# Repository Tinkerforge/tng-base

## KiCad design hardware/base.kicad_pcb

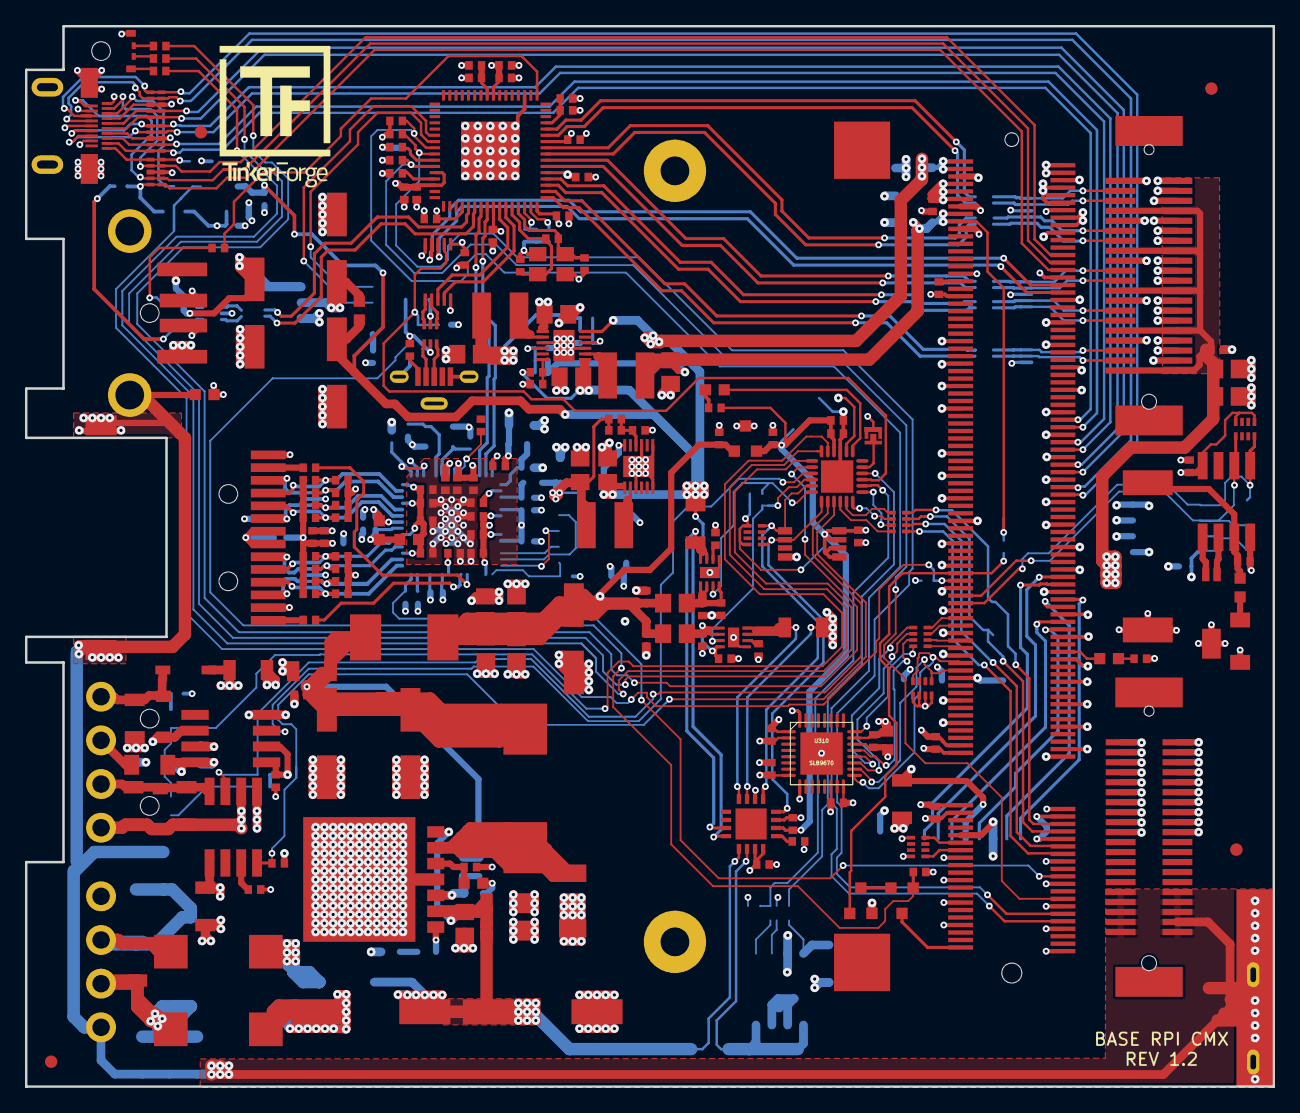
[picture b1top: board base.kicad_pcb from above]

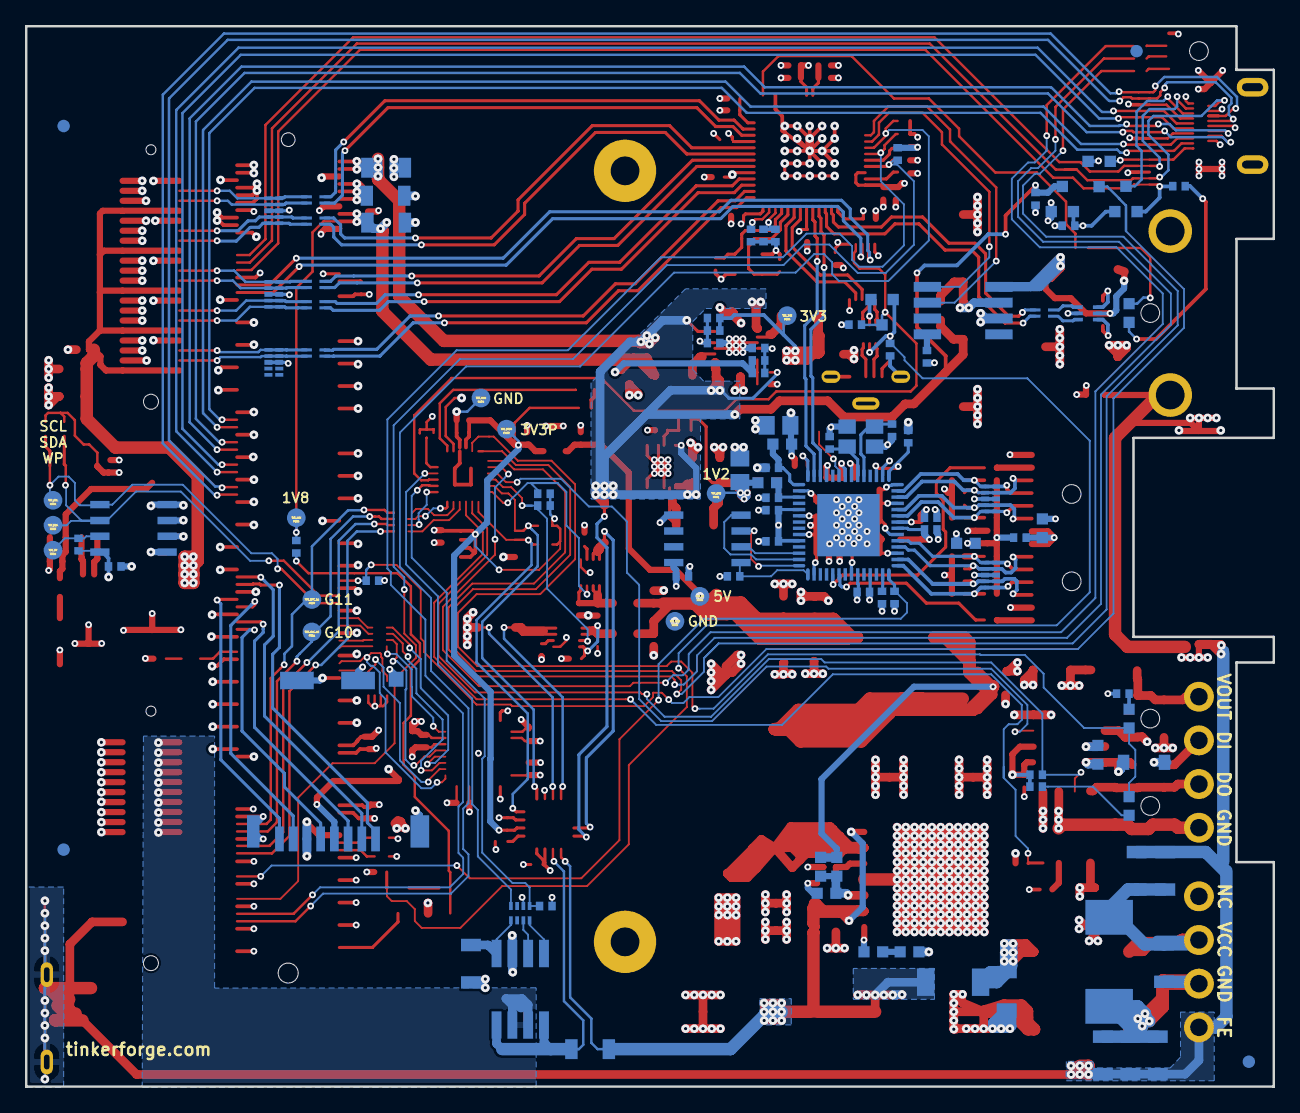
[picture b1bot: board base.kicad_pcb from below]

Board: 4 copper layers, 100.0 x 85.0 mm, 315 parts (112 on the bottom side), 207 nets.

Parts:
C101, C102, C421, C422: 33pF; C0402F
C103, C105, C115, C119, C122, C123, C124, C125, C126, C127, C128, C129, C130, C134, C307, C308, C310: 1uF; C0402F
C104, C106, C107, C110, C111, C112, C113, C114, C116, C118, C121, C133, C214, C221, C222, C227, C302, C315, C316, C318, C319, C321, C323, C325, C327, C402, C403, C404, C405, C406, C407, C408, C409, C411, C412, C413, C414, C415, C416, C417, C418, C419, C420, C430, C433: 100nF; C0402F
C108, C109, C117, C216, C219, C220: 100uF; ELKO_63
C120: 100nF; C0603F
C131, C132, C322, C324: DNP; C0402F
C135, C136, C218, C223, C224, C225, C301, C303, C309, C311, C401, C410, C435, C437: 10uF; C0805E
C201, C202, C203: 10uF/35V; C1206
C204, C211: 10nF; C1206
C205: 100nF/35V; C0805E
C206, C207: 1nF 2kV; C1206
C208, C305, C306, C436: 100pF; C0402F
C209: 1uF/50V; C1206
C210: 4.7nF; C0603F
C212, C213: UWT1H221MNL1GS; ELKO_103
C215, C226: 10uF; C1206
C217: DNP; C0603F
C304, C312, C313, C314: 47uF; C1206
C317: DSK-3R3H334T-HL; DSK
C320: 2.2uF; C0603F
C423, C424, C425, C426, C427, C429, C431, C432: 15pF/50V; C0402F
C428: 10nF; C0402F
C434: 22nF/50V; C0603F
D101: LED green; LED-LP
D201: 3.0SMI30CATR; SMC
D202, D204, D209: SMF36CA; SOD-123FL
D203: SBR0560S1-7; SOD-123
D205, D206: PMEG6045; SOD-128
D207, D210: LED; LED-LP
D208: LED; D0603F
D301: green; D0603F
D302: BAQ33-GS08; MiniMelf
Fiducial_Mark: VAL**; Fiducial_Mark
Fiducial_Mark#2, Fiducial_Mark#3, Fiducial_Mark#4, Fiducial_Mark#5, Fiducial_Mark#6, Fiducial_Mark#7, Fiducial_Mark#8: VAL**; Fiducial_Mark
J101: USB-A; USB-A-SMT-8231
J102: TNG-Data-TOP; TNG-40-TOP
J103: TNG-Power-TOP; TNG-40-TOP
J301: MICROSDCARD; SD-Card-DM3CS
J302: Raspberry-Pi-Compute-Socket
J303: MICRO_HDMI; MICRO-HDMI-D
J304: USB Micro; USB-Micro-Vertical
J401: RJSLG-001TA1
L101: INDUCTs; R0603F
L102, L103, L104, L105, L106, L107: 744230900; WE-CNSW-0603
L108, L109: 742792040; R0805E
L202: 22uH 74437368220; WE-LHMI
L203: 10uH; SRP7030
L301: 4.7uH; NR4040
L302, L406: 2.2uH; NR4040
L401, L402, L403, L404, L405: FB; R0603F
LED101: EASV3015RGBA0; LED-RGB-LP
P101: Debug; DEBUG_PAD
P102: Boot; SolderJumper
P103: PE; PE_Hook
P104, P204: TST_GND; TSTPT
P105: TST_3V3P; TSTPT
P201: DI IN; OQ_4P
P202: PWR IN; OQ_4P
P203: TST_5V; TSTPT
P301: TST_XMC_10; TSTPT
P302: TST_SCL; TSTPT
P303: TST_SDA; TSTPT
P304: TST_WP; TSTPT
P305: TST_3V3; TSTPT
P306: TST_1V8; TSTPT
P307: TST_XMC_11; TSTPT
P401: TST_1V2; TSTPT
Q301, Q302, Q303, Q304, Q305: 2N7002P; SOT23GDS
R101, R105, R106, R107, R108, R111, R115, R116, R117, R218, R305, R320, R401, R402, R406, R414: 10k; R0402F
R102, R210, R301, R302, R304, R316, R419, R420: 100k; R0402F
R103: 1M; R0402F
R104, R213, R216, R217, R222, R309, R416, R417: 1k; R0402F
R109, R403: DNP; R0402F
R110, R405: 12k; R0402F
R112, R113, R315: 0; R0402F
R114: 56; R0402F
R118: 1k; R1206
R201, R202, R204, R206, R207: VC1206K201R030; R1206
R203: 1k; RMELF
R205: 562; R0603F
R208: 27k; R0603F
R209: 1M; R1206
R211: 562; R0402F
R212: 20k; R0603F
R214: 47k; R0603F
R215: 8.2k; R0603F
R219, R220, R221: 0.02; R1206
R303: 120k; R0402F
R306: 536k; R0402F
R307: 200k; R0402F
R313, R317, R318: 47k; R0402F
R314: 68; R0603F
R319: 27k; R0402F
R404: 8.06k; R0402F
R407, R408, R409, R410, R411, R412, R413, R415: 49.9; R0402F
R418: 10; R0402F
RP101, RP102, RP303, RP305: 10k; 4X0402
RP301, RP304: 82; 4X0402
RP302: 100k; 4X0402
T201: 744272251; WE-SL5
U101: USB2517; QFN64-9x9mm-0.5mm_USB2517
U102: MIC2026-1YM; SO-8
U103, U307: 82400152; SOT563-SPEC
U104: XMC1302; QFN24-4x4mm-0.5mm
U105, U106, U107, U304, U305, U306, U403, U404: TPD4S010DQA
U108: AP7333-33SAG-7; SOT23-3
U109, U110: TPS22975; WSON8-2x2
U111: PCT2075DP; TSSOP8_3
U112: VN7140AS; SO-8
U201: ISO1211; SO-8
U202: FPF2700MX; SO-8
U203: BD90640HFP; BD906XX-C-HRP7
U204: PAC1933; QFN-16
U301, U405: PAM2306AYPAA; WDFN12-3x3-0.45
U302: PCF8523T; SO-8
U303: FSUSB42MUX; MSOP10-0.5
U308: M24256-DFMN6TP; SOIC8
U309: AP2331; SOT23-3
U310: SLB9670; QFN32-EXT
U401: LAN7500; QFN56-8x8mm-0.5mm
U402: 93AA66; SOIC8
X101: 24MHz; CRYSTAL_3225
X301: 32.768kHz; AB26TRQ
X401: 25MHz_18pF; CRYSTAL_3225

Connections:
3V3: C110.1, C111.1, C112.1, C113.1, C114.1, C115.1, C116.1, C118.1, C119.1, C304.1, C305.1, C307.1, C308.2, C309.1, C310.1, C313.1, C315.1, C318.2, C319.2, C320.2, C322.1, C323.1, C324.1, C325.1, C401.1, C402.1, C403.1, C404.1, C406.1, C433.1, D101.1, D302.1, J301.4, J302.39, J302.40, J302.41, J302.42, J302.189, J302.190, J302.191, J302.192, J302.193, J302.194, J401.12, J401.14, L301.2, L403.2, L405.1, P305.1, R101.2, R102.2, R106.2, R108.2, R111.2, R305.1, R306.1, R309.2, R316.1, R317.2, R319.1, R401.2, R402.2, R406.1, RP303.1, RP303.4, RP305.1, RP305.2, RP305.3, RP305.4, U101.5, U101.10, U101.24, U101.44, U101.46, U101.52, U101.57, U101.64, U302.8, U303.1, U308.8, U310.1, U310.8, U310.14, U310.22, U401.7, U401.19, U401.24, U401.37, U402.8
3V3_PERM: C121.1, C122.1, C130.1, C133.1, C221.1, C222.1, C227.2, LED101.1, P105.1, R115.2, R116.2, R117.2, R210.2, R213.1, R216.2, R217.2, RP101.5, RP101.8, RP102.2, U104.10, U108.2, U111.5, U111.6, U111.7, U111.8, U201.1, U201.2, U204.2, U204.6, U204.15, U204.16
5VSW: C108.1, C301.1, C303.1, C314.1, C321.1, C435.1, J302.197, J302.198, J302.199, J302.200, L101.2, R219.2, R301.2, U204.12, U301.1, U301.6, U301.7, U309.3, U405.6, U405.7
5VStack: C134.2, C135.2, C136.2, J102.7, J102.8, J102.15, J102.16, J102.23, J102.24, J102.31, J102.32, J102.39, J102.40, R221.2, U204.7
+1.2V: C410.1, C411.1, C412.1, C413.1, C414.1, C415.1, C417.1, C418.1, C436.1, C437.1, L401.2, L402.2, L404.2, L406.2, P401.1, R420.1, U401.8, U401.11, U401.20, U401.23, U401.30, U401.36, U401.49
+1.2V_INT: C405.1, C407.1, C408.1, C409.1, L401.1, U401.45, U401.48, U401.53, U401.56
+1.8V: C306.1, C311.1, C312.1, J302.183, J302.184, J302.185, J302.186, L302.2, P306.1, R304.2, R307.1
+3.3VP: C420.1, L403.1, U401.15
+5V: C123.2, C125.2, C129.1, C218.1, C219.1, C223.1, C224.1, C225.1, L108.1, L109.1, L203.2, P203.1, U108.1
AGND: C101.2, C102.2, C103.2, C104.2, C105.2, C106.2, C107.2, C108.2, C109.2, C110.2, C111.2, C112.2, C113.2, C114.2, C115.2, C116.2, C117.2, C118.2, C119.2, C120.2, C121.2, C122.2, C123.1, C124.1, C125.1, C126.1, C127.2, C128.2, C129.2, C130.2, C131.2, C132.2, C133.2, C134.1, C135.1, C136.1, C201.2, C202.2, C203.1, C205.2, C208.2, C209.2, C210.2, C211.2, C212.2, C213.2, C214.2, C215.2, C216.2, C218.2, C219.2, C220.2, C221.2, C222.2, C223.2, C224.2, C225.2, C226.1, C227.1, C301.2, C302.2, C303.2, C304.2, C307.2, C308.1, C309.2, C310.2, C311.2, C312.2, C313.2, C314.2, C315.2, C316.2, C317.2, C318.1, C319.1, C320.1, C321.2, C322.2, C323.2, C324.2, C325.2, C327.2, C401.2, C402.2, C403.2, C404.2, C405.2, C406.2, C407.2, C408.2, C409.2, C410.2, C411.2, C412.2, C413.2, C414.2, C415.2, C416.2, C417.2, C418.2, C419.2, C420.2, C421.2, C422.2, C423.2, C424.2, C425.2, C426.2, C427.2, C428.2, C429.2, C430.2, C431.2, C432.2, C433.2, C434.2, C435.2, C437.2, D202.2, D204.2, D206.1, D209.2, J101.4, J102.1, J102.2, J102.4, J102.6, J102.9, J102.10, J102.12, J102.14, J102.17, J102.18, J102.20, J102.22, J102.25, J102.26, J102.28, J102.30, J102.33, J102.34, J102.36, J102.38, J103.2, J103.4, J103.6, J103.8, J103.10, J103.12, J103.14, J103.16, J103.18, J103.20, J301.6, J301.S, J302.1, J302.7, J302.8, J302.13, J302.14, J302.19, J302.20, J302.25, J302.26, J302.31, J302.32, J302.37, J302.38, J302.43, J302.44, J302.49, J302.50, J302.55, J302.56, J302.61, J302.62, J302.67, J302.68, J302.73, J302.74, J302.79, J302.80, J302.85, J302.86, J302.91, J302.92, J302.97, J302.98, J302.103, J302.104, J302.109, J302.110, J302.115, J302.116, J302.121, J302.122, J302.127, J302.133, J302.134, J302.139, J302.140, J302.145, J302.146, J302.151, J302.152, J302.157, J302.163, J302.164, J302.169, J302.170, J302.181, J302.182, J302.187, J302.188, J302.195, J302.196, J303.4, J303.7, J303.10, J303.13, J303.16, J303.SHD, J304.5, J304.6, P102.1, P104.1, P201.4, P204.1, Q301.S, Q303.S, Q304.S, R105.1, R107.2, R109.2, R110.1, R118.1, R201.1, R202.2, R208.1, R211.2, R215.1, R218.2, R222.2, R302.1, R303.1, R313.1, R315.1, R318.1, R404.1, R405.1, R414.1, R419.1, RP302.5, RP302.8, T201.1, U101.19, U101.EXP, U102.6, U103.2, U104.9, U104.EXP, U105.3, U105.8, U106.3, U106.8, U107.3, U107.8, U108.3, U109.5, U109.EXP, U110.5, U110.EXP, U111.4, U112.3, U201.4, U201.6, U202.5, U202.6, U203.4, U203.EXP, U204.3, U301.3, U301.9, U301.EP, U302.4, U303.5, U303.10, U304.3, U304.8, U305.3, U305.8, U306.3, U306.8, U307.2, U308.1, U308.2, U308.3, U308.4, U309.1, U310.2, U310.9, U310.16, U310.23, U310.32, U310.33, U401.2, U401.39, U401.EP, U402.5, U403.3, U403.8, U404.3, U404.8, U405.1, U405.3, U405.9, U405.12, U405.EP, X101.3, X301.3, X401.3
CUR1+: R219.1, U109.7, U109.8, U204.11
CUR2+: C201.1, C202.1, C203.2, C205.1, C212.1, C213.1, C226.2, D203.1, D205.2, R220.1, U202.1, U203.2, U203.7, U204.13
CUR2-: R220.2, U112.5, U112.8, U204.14
CUR3+: R221.1, U110.7, U110.8, U204.8
EECLK: U401.26, U402.2
EECS: R414.2, U401.29, U402.1
EEDI: U401.27, U402.4
EEDO: U401.28, U402.3
ETH_RESET: J302.21, R401.1, U401.42
ETH_USB_D+: U101.56, U401.13
ETH_USB_D-: U101.55, U401.12
EXT_USB_D+: L102.2, U101.54
EXT_USB_D-: L102.3, U101.53
EXT_USB_D_F+: J101.3, U103.4
EXT_USB_D_F-: J101.2, U103.6
Earth: C120.1, C206.2, C207.1, J101.SHD, J103.31, J103.32, J103.33, J103.34, J103.35, J103.36, J103.37, J103.38, J103.39, J103.40, J401.SHD, P103.1, P202.4, R206.2, R207.1, R209.1
FLASH_USB_D+: U303.7, U307.1
FLASH_USB_D-: U303.6, U307.3
FLASH_USB_D_F+: J304.3, U307.6
FLASH_USB_D_F-: J304.2, U307.4
HDMI_5V: C327.1, J303.19, Q305.G, U309.2
HDMI_CEC: J302.171, Q305.S, R319.2, U306.1, U306.10
HDMI_CLK+: J302.113, J303.12, U305.4, U305.7
HDMI_CLK-: J302.111, J303.14, U305.5, U305.6
HDMI_D0+: J302.119, J303.9, U305.1, U305.10
HDMI_D0-: J302.117, J303.11, U305.2, U305.9
HDMI_D1+: J302.125, J303.6, U304.4, U304.7
HDMI_D1-: J302.123, J303.8, U304.5, U304.6
HDMI_D2+: J302.131, J303.3, U304.1, U304.10
HDMI_D2-: J302.129, J303.5, U304.2, U304.9
HDMI_SCL: J302.175, J303.17, U306.4, U306.7
HDMI_SDA: J302.173, J303.18, U306.2, U306.9
LED_ACT: R416.1, U401.33
LED_LINK: R417.1, U401.34
unnamed: C101.1, R103.2, U101.61, X101.1
unnamed: C102.1, R103.1, U101.60, X101.2
unnamed: C103.1, C104.1, U101.25
unnamed: C105.1, C106.1, U101.62
unnamed: C109.1, L101.1, U102.7
unnamed: C124.2, C127.1, L108.2, U109.1, U109.2, U109.4
unnamed: C126.2, C128.1, L109.2, U110.1, U110.2, U110.4
unnamed: C131.1, U109.6
unnamed: C132.1, U110.6
unnamed: C204.1, C206.1, D201.1, P202.2, R204.1, R206.1, T201.3
unnamed: C204.2, C207.2, D201.2, P202.3, R204.2, R207.2, R209.2, T201.4
unnamed: C208.1, R208.2, U203.5
unnamed: C209.1, D204.1, P201.3, R202.1, U202.8
unnamed: C210.1, R212.1
unnamed: C211.1, D205.1, T201.2
unnamed: C214.1, C215.1, C216.1, C217.1, C220.1, L202.2, L203.1, R214.2
unnamed: C217.2, R214.1, R215.2, U203.3
unnamed: C302.1, R301.1, U301.12
unnamed: C305.2, R303.2, R306.2, U301.4
unnamed: C306.2, R302.2, R307.2, U301.10
unnamed: C316.1, C317.1, R314.1, U302.3
unnamed: C421.1, U401.5, X401.1
unnamed: C422.1, U401.6, X401.2
unnamed: C428.1, C430.1, L405.2, R407.2, R408.2, R409.2, R410.2, R411.2, R412.2, R413.2, R415.2, R418.2
unnamed: C434.1, J401.5, J401.6, R418.1
unnamed: C436.2, R419.2, R420.2, U405.4
unnamed: D101.2, R104.2
unnamed: D202.1, D203.2, P201.1, R201.2
unnamed: D206.2, L202.1, U203.6
unnamed: D207.1, R216.1
unnamed: D208.1, R217.1
unnamed: D209.1, R203.2, R205.1, U201.8
unnamed: D210.2, R222.1
unnamed: D301.1, R309.1
unnamed: D301.2, J302.69
unnamed: D302.2, R314.2
unnamed: J302.2, Q302.D
unnamed: J302.27, RP301.1
unnamed: J302.28, RP302.1
unnamed: J302.29, RP301.2
unnamed: J302.30, RP302.4
unnamed: J302.33, P301.1, RP301.3
unnamed: J302.35, P307.1, RP301.4
unnamed: J302.70, RP304.1
unnamed: J302.72, RP304.2
unnamed: J302.76, RP304.3
unnamed: J302.78, RP304.4
unnamed: J302.82, P302.1, RP303.8, U302.5, U308.5
unnamed: J302.84, P303.1, RP303.5, U302.6, U308.6
unnamed: J302.88, Q303.D, R316.2
unnamed: J302.90, Q301.G, R304.1
unnamed: J302.168, R315.2
unnamed: J303.1, Q303.G, U306.5, U306.6
unnamed: J303.15, Q305.D
unnamed: J304.1, R320.2
unnamed: J401.11, R417.2
unnamed: J401.13, R416.2
unnamed: L102.1, U103.3
unnamed: L102.4, U103.1
unnamed: L301.1, U301.8
unnamed: L302.1, U301.2
unnamed: L406.1, U405.8
unnamed: LED101.2, R112.2
unnamed: LED101.3, R113.2
unnamed: LED101.4, R114.2
unnamed: P101.1, U104.8
unnamed: P102.2, U104.5
unnamed: P201.2, R203.1
unnamed: P304.1, R305.2, U308.7
unnamed: Q301.D, Q302.S
unnamed: R101.1, U101.45
unnamed: R104.1, U101.17
unnamed: R105.2, U102.4
unnamed: R107.1, U101.42
unnamed: R108.1, R109.1, U101.13
unnamed: R110.2, U101.63
unnamed: R112.1, U104.14
unnamed: R113.1, U104.13
unnamed: R114.1, U104.12
unnamed: R118.2, RP102.5, U112.4
unnamed: R205.2, U201.7
unnamed: R211.1, U202.3
unnamed: R212.2, U203.1
unnamed: R218.1, U204.1
unnamed: R402.1, U401.1, U401.3
unnamed: R403.2, U401.9
unnamed: R404.2, U401.41
unnamed: R405.2, U401.16
unnamed: R406.2, U401.14
unnamed: RP102.7, U112.2
unnamed: RP102.8, U112.1
unnamed: U101.38, U102.2
unnamed: U101.39, U102.1
unnamed: U302.1, X301.2
unnamed: U302.2, X301.1
ORIG_USB_D+: J302.165, U303.3
ORIG_USB_D-: J302.167, U303.4
RASP_USB_D+: U101.59, U303.9
RASP_USB_D-: U101.58, U303.8
RASP_USB_RESET: C107.1, J302.15, R102.1, U101.43
RASP_USB_SMB_CLK: J302.11, R111.1, U101.41
RASP_USB_SMB_DATA: J302.9, R106.1, U101.40
SD1_CLK: J301.5, J302.75
SD1_CMD: J301.3, J302.77
SD1_DAT0: J301.7, J302.81
SD1_DAT1: J301.8, J302.83
SD1_DAT2: J301.1, J302.87
SD1_DAT3: J301.2, J302.89
STACKPWR: J103.1, J103.3, J103.5, J103.7, J103.9, J103.11, J103.13, J103.15, J103.17, J103.19, U112.6, U112.7
STACK_USB_D0+: L103.2, U101.12
STACK_USB_D0-: L103.3, U101.11
STACK_USB_D0_F+: J102.3, L103.1, U105.5, U105.6
STACK_USB_D0_F-: J102.5, L103.4, U105.4, U105.7
STACK_USB_D1+: L104.2, U101.9
STACK_USB_D1-: L104.3, U101.8
STACK_USB_D1_F+: J102.11, L104.1, U105.2, U105.9
STACK_USB_D1_F-: J102.13, L104.4, U105.1, U105.10
STACK_USB_D2+: L105.2, U101.7
STACK_USB_D2-: L105.3, U101.6
STACK_USB_D2_F+: J102.19, L105.1, U106.5, U106.6
STACK_USB_D2_F-: J102.21, L105.4, U106.4, U106.7
STACK_USB_D3+: L106.2, U101.4
STACK_USB_D3-: L106.3, U101.3
STACK_USB_D3_F+: J102.27, L106.1, U106.2, U106.9
STACK_USB_D3_F-: J102.29, L106.4, U106.1, U106.10
STACK_USB_D4+: L107.2, U101.2
STACK_USB_D4-: L107.3, U101.1
STACK_USB_D4_F+: J102.35, L107.1, U107.5, U107.6
STACK_USB_D4_F-: J102.37, L107.4, U107.4, U107.7
TPM_CS: RP304.5, U310.20
TPM_IRQ: J302.64, RP305.5, U310.18
TPM_MISO: RP304.8, U310.24
TPM_MOSI: RP304.7, U310.21
TPM_RST: J302.66, RP305.8, U310.17
TPM_SCLK: RP304.6, U310.19
TR0_N: C424.1, J401.2, R408.1, U401.43, U403.1, U403.10
TR0_P: C423.1, J401.1, R407.1, U401.44, U403.2, U403.9
TR1_N: C426.1, J401.4, R410.1, U401.46, U403.4, U403.7
TR1_P: C425.1, J401.3, R409.1, U401.47, U403.5, U403.6
TR2_N: C429.1, J401.8, R412.1, U401.51, U404.1, U404.10
TR2_P: C427.1, J401.7, R411.1, U401.52, U404.2, U404.9
TR3_N: C432.1, J401.10, R415.1, U401.54, U404.4, U404.7
TR3_P: C431.1, J401.9, R413.1, U401.55, U404.5, U404.6
USB-PWR: C117.1, J101.1, U102.8, U103.5
VBUSB: Q302.G, Q304.G, R313.2, R318.2, R320.1, U307.5
VDD12PLL: C419.1, L404.1, U401.50
VDD12USBPLL: C416.1, L402.1, U401.17
XMC_CLK: RP301.5, U104.23
XMC_CS: RP301.8, U104.22
XMC_DI0: U104.15, U201.3
XMC_DI1: R210.1, U104.20, U202.7
XMC_DO0: R213.2, U104.21, U202.4
XMC_LED_PWR: D208.2, U104.7
XMC_MISO: RP301.7, U104.1
XMC_MOSI: RP301.6, U104.24
XMC_MUSB_CON: Q304.D, R317.1, U104.3, U303.2
XMC_PORT_LED: D207.2, D210.1, U104.11
XMC_SCL: RP101.1, U104.19, U111.2, U204.4
XMC_SDA: RP101.4, U104.17, U111.1, U204.5
XMC_SW_5V: R115.1, U104.18, U109.3
XMC_SW_PWR: R117.1, RP102.1, U104.2
XMC_SW_PWR_CUR: RP102.4, U104.4
XMC_SW_STACK: R116.1, U104.16, U110.3

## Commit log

2020-05-12 Convert readme to rST
2020-05-12 image: Add initial balenaOS testing
2020-05-13 moved files to new repository
2020-05-14 image: Fix typo in docker config
2020-05-14 image: Use balena-idle instead of open coding it
2020-05-14 image: Don't override docker image names for now
    This make local balena-push fail, because it expects to see its
    autogenerated image names. Overriding them makes the supervisor
    not find them.
2020-05-14 image: Switch brickd container base from Debian to Alpine
2020-05-15 start version 1.2:
    * fix cryptochip i2c connections
2020-05-15 image: Document Raspberry Pi bootloader config changes
2020-05-15 Add some datasheets
2020-05-18 fix rtc diode
2020-06-24 change pcb silkscreen name
2020-07-02 raspbian: Add initramfs for setting device specific password
2020-07-02 balena: Move files to subdirectory
2020-07-02 balena: Move config.txt file
2020-07-08 raspbian: Add initial crypto chip support to initramfs
2020-07-08 image: Enable SPI for TNG Base Bricklet
2020-07-13 add remark
2020-07-14 raspbian: Only replace default password if it is locked as well
    Locking the default password ensures that even if password replacement
    fails for some reason that the default password can never be used.
2020-07-14 raspbian: Rename username to account in initramfs
2020-07-24 raspbian: Add micro SD card and TPM config.txt
2020-07-24 Remove obsolete files
2020-07-24 Add datasheet for Ethernet chip
2020-07-24 raspbian: Add GPL header
2020-07-24 raspbian: Link init programm to zlib for crc32 function
    CRC32 checksum will be used for EEPROM content validation.
2020-07-28 improve ethernet thermal design improve 1.2V generation
2020-07-28 raspbian: Drop cryptoauthlib usage
2020-07-28 raspbian: Add error function to initramfs
2020-07-28 raspbian: Avoid initial warning for mounting the root file system
2020-07-28 raspbian: Make initramfs use EEPROM for device specific password storage
2020-07-30 add heatsink draft
2020-08-06 add tpm module
2020-08-07 raspbian: Add initial version of EEPROM tool
2020-08-07 raspbian: Unify initramfs error message style
2020-08-07 raspbian: Extend initramfs panic reboot delay to 60 seconds
2020-08-07 raspbian: Fix NULL pointer dereference in reboot trigger logic
2020-08-07 raspbian: Fix syntax error in initramfs
2020-08-07 raspbian: Rename /root to /mnt in initramfs log messages to avoid confusion
2020-08-07 raspbian: Fix mode usage in initramfs create_file function
2020-08-07 raspbian: Add Ethernert EEPROM config and /etc/tng-base-* logic to initramfs
2020-08-07 raspbian: Add missing part of /root to /mnt change in initramfs
2020-08-07 raspbian: Add Debian package script for initramfs
2020-08-12 raspbian: Remove cmdline.txt and config.txt from bootloader package
    Those files are modified by various tools as runtime. It's easier to
    not have them packaged, the same way vanilly Raspbian does it.
2020-08-14 raspbian: Add hwclock --hctosys logic to initramfs
2020-08-14 Add EEPROM datasheet
2020-08-18 add testpoints for power supplies, flash interface
2020-08-19 raspbian: Use root, rootfstype and init kernel cmdline options in initramfs
    Use libmount in initramfs to support mounting by PARTUUID.
    Need to mount devtmpfs at /dev to make libmount and libblkid work properly.
    Adding support for the init kernel cmdline option allows Raspbian's file
    system resize script to work. This required to have devtmpfs mounted at /dev
    in the root-mount, as the kernel would normally do, otherwise "mount /" in
    the resize script does not work.
2020-08-19 raspbian: Fix typo in initramfs log message
2020-08-19 raspbian: Add some missing prints in initramfs error paths
2020-08-21 ordered version 1.2
    add testpoints
2020-09-04 fix text
2020-09-04 specify capacitor voltages
2020-09-04 fix capacitor footprints
2020-09-07 fix capacitor values
2020-09-07 fix footprints
2020-09-07 fix footprint
2020-09-07 fix values
2020-09-08 specify processor
2020-09-08 fix capacitor value
2020-09-08 all footprints updated
2020-09-09 fix outline
2020-09-09 change ethernet capacitors to 33pF
2020-09-09 change slb capacitor
2020-09-10 fix 3d stuff
2020-09-28 add hint
2020-10-06 fix footprint type

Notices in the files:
hardware/base.kicad_pcb:
Licensed under CERN OHL v.1.1
Copyright (©) 2020, B.Nordmeyer
Copyright Tinkerforge GmbH 2020.
This documentation describes Open Hardware and is licensed under the
CERN OHL v. 1.1.
